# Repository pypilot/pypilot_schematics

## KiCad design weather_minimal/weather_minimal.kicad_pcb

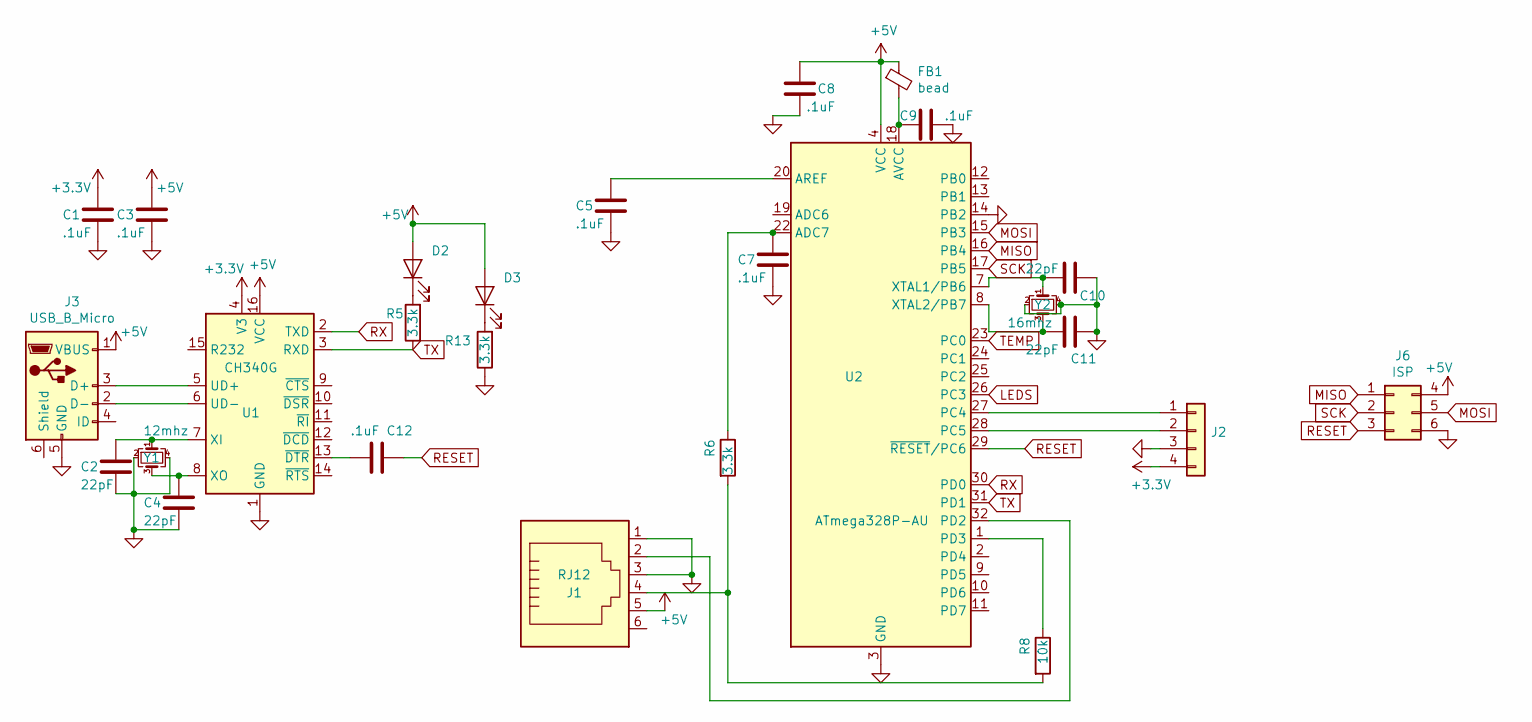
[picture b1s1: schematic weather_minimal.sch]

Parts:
C1, C3, C5, C7, C8, C9, C12: .1uF; C_0805_2012Metric; LCSC C49678
C2, C4, C10, C11: 22pF; C_0805_2012Metric; LCSC C1804
D2: LED2; LED_0805_2012Metric; LCSC C2296
D3: LED3; LED_0805_2012Metric; LCSC C84256
FB1: bead; L_0805_2012Metric; LCSC C1017
J1: RJ12; RJ12_E; LCSC C305981
J2: Conn_01x04; 1X04
J3: USB_B_Micro; USB_Mini-B_Tensility_54-00023_Vertical
J6: ISP
R5, R6, R13: 3.3k; R_0805_2012Metric; LCSC C26010
R8: 10k; R_0805_2012Metric; LCSC C17414
U1: CH340G; SOIC-16_3.9x9.9mm_P1.27mm; LCSC C14267
U2: ATmega328P-AU; TQFP-32_7x7mm_P0.8mm; LCSC C132230
Y1: 12mhz; Crystal_SMD_3225-4Pin_3.2x2.5mm; LCSC C9002
Y2: 16mhz; Crystal_SMD_3225-4Pin_3.2x2.5mm; LCSC C13738

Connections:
+3V3: C1.1, J2.4, U1.4 (V3)
+5V: C3.1, C8.2, D2.2 (A), D3.2 (A), FB1.1, J1.5, J3.1 (VBUS), J6.4, U1.16 (VCC), U2.4 (VCC), U2.6 (VCC)
GND: C1.2, C2.2, C3.2, C4.2, C5.2, C7.2, C8.1, C9.1, C10.1, C11.1, J1.1, J1.3, J2.3, J3.5 (GND), J6.6, R13.1, U1.1 (GND), U2.3 (GND), U2.5 (GND), U2.14 (PB2), U2.21 (GND), Y1.2, Y1.4, Y2.2, Y2.4
LEDS: U2.26 (PC3)
MISO: J6.1, U2.16 (PB4)
MOSI: J6.5, U2.15 (PB3)
unnamed: C2.1, U1.7 (XI), Y1.1
unnamed: C4.1, U1.8 (XO), Y1.3
unnamed: C5.1, U2.20 (AREF)
unnamed: C7.1, R6.1, U2.22 (ADC7)
unnamed: C9.2, FB1.2, U2.18 (AVCC)
unnamed: C10.2, U2.7 (XTAL1/PB6), Y2.1
unnamed: C11.2, U2.8 (XTAL2/PB7), Y2.3
unnamed: C12.2, U1.13 (~DTR)
unnamed: D2.1 (K), R5.2
unnamed: D3.1 (K), R13.2
unnamed: J1.2, U2.32 (PD2)
unnamed: J1.4, R6.2, R8.2
unnamed: J2.1, U2.27 (PC4)
unnamed: J2.2, U2.28 (PC5)
unnamed: J3.2 (D-), U1.6 (UD-)
unnamed: J3.3 (D+), U1.5 (UD+)
unnamed: R8.1, U2.1 (PD3)
RESET: C12.1, J6.3, U2.29 (~RESET~/PC6)
RX: U1.2 (TXD), U2.30 (PD0)
SCK: J6.2, U2.17 (PB5)
TEMP: U2.23 (PC0)
TX: R5.1, U1.3 (RXD), U2.31 (PD1)

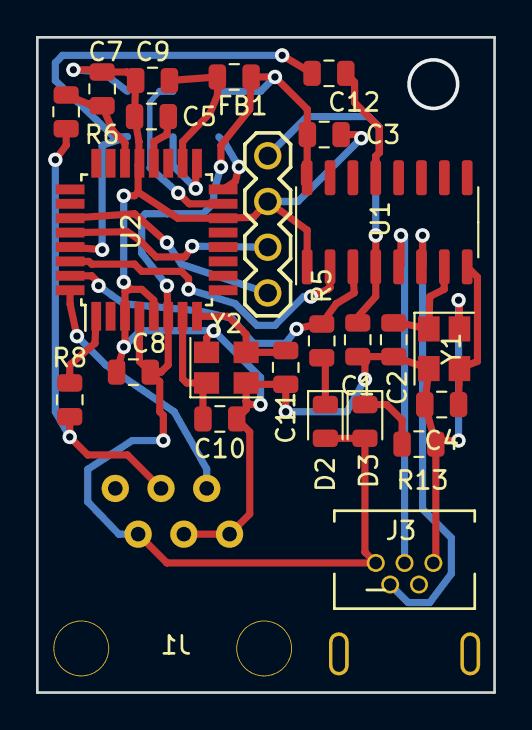
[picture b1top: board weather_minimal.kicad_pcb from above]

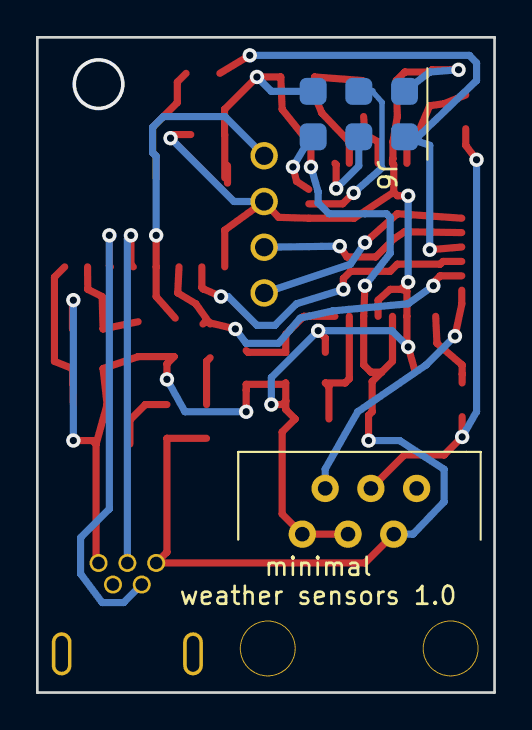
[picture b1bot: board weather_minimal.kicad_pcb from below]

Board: 2 copper layers, 25.4 x 36.4 mm, 26 parts (2 on the bottom side), 26 nets.

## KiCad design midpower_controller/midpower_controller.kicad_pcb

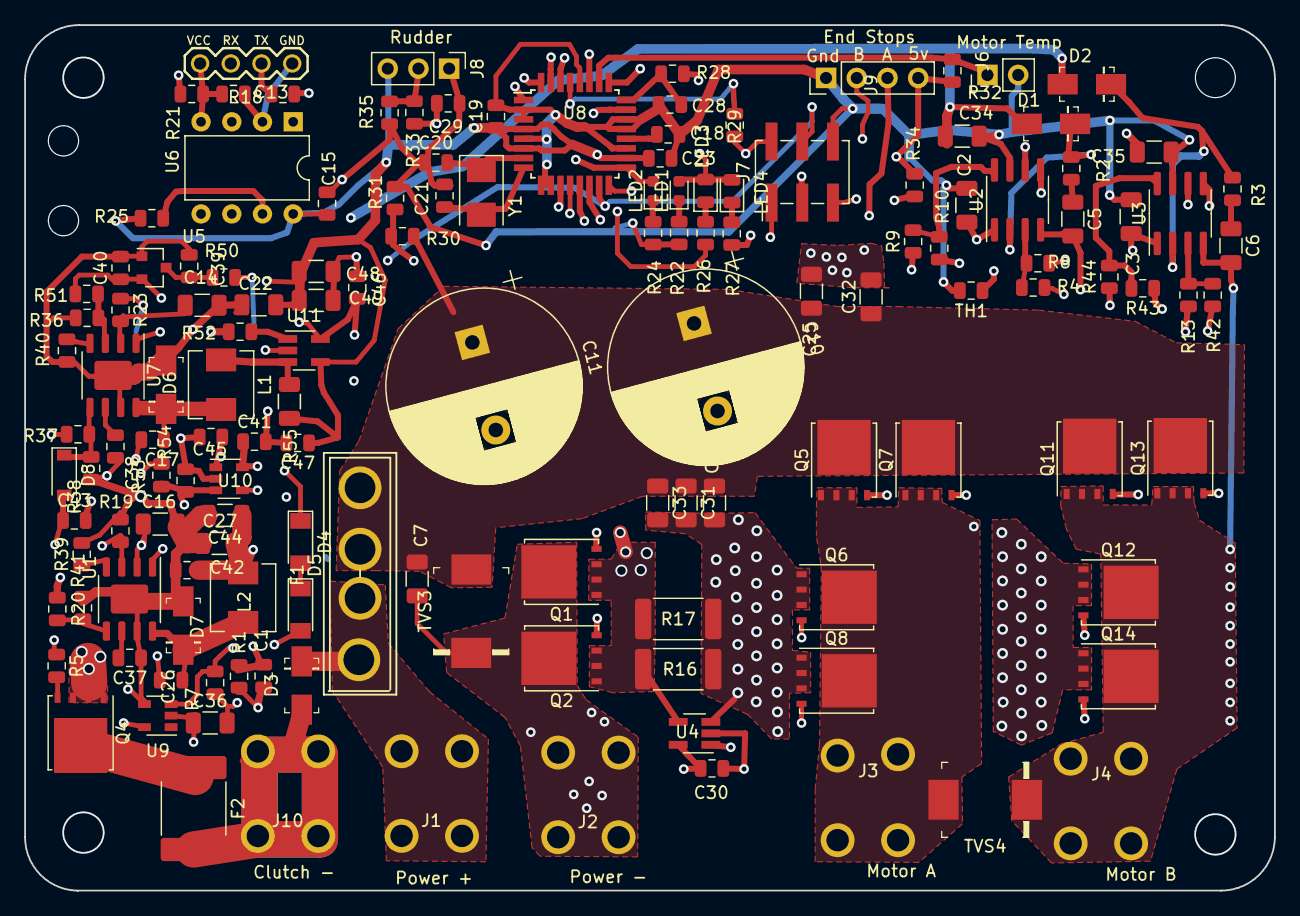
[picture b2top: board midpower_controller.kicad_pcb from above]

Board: 4 copper layers, 103.4 x 71.6 mm, 142 parts (0 on the bottom side), 81 nets.

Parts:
C1: 1uF; C_0805_2012Metric
C2, C3, C5, C6, C7, C14, C16, C22, C24, C25, C27, C31, C32, C33, C34, C35, C36, C44, C48, C49: 10uF; C_1206_3216Metric
C10, C11: 680uF; CP_Radial_D16.0mm_P7.50mm
C13, C15, C18, C19, C23, C28, C29, C30, C41, C42, C45, C46, C47: .1uF; C_0805_2012Metric
C17, C26: .22uF; C_0805_2012Metric
C20: 18pF; C_0805_2012Metric
C21: 12pF; C_0805_2012Metric
C37, C38, C43: 22nF; C_0805_2012Metric
C39, C40: 4.7uF; C_0805_2012Metric
D1: MUR160, ES1DHE3; DO-214AC
D2, D3: MUR160; DO-214AC
D4, D5: 5.6v; D_MiniMELF
D6, D7: D; DO-214AC
D8: D; D_SOD-123
F1: FUSE; BladeFuse-CarType
F2: FUSE; Fuse_2920_7451Metric
J1, J3, J4: power+; screw_terminal
J2, J10: power-; screw_terminal
J5: UART_Device; uart
J6: Conn_01x02; PinHeader_1x02_P2.54mm_Vertical
J7: ISP; PinHeader_2x03_P2.54mm_Vertical_SMD
J8: Rudder; PinHeader_1x03_P2.54mm_Vertical
J9: End Stops; PinHeader_1x04_P2.54mm_Vertical
L1, L2: 10uH; L_Sunlord_MWSA0518_5.4x5.2mm
LED1: RED; LED_0603_1608Metric
LED2: BLUE; LED_0603_1608Metric
LED3: GREEN; LED_0805_2012Metric
LED4: YELLOW; LED_0805_2012Metric
Q1, Q2, Q4, Q5, Q6, Q7, Q8, Q11, Q12, Q13, Q14: Q_NMOS_GDS; TDSON-8-1
R1, R7, R29, R32, R34, R38, R41, R52, R54: 10k; R_0805_2012Metric
R2, R3: 2.2; R_0805_2012Metric
R4, R5, R8, R9, R10, R13, R42, R43, R44: 47; R_0805_2012Metric
R16, R17: 2m; R_2512_6332Metric
R18, R50: 560; R_0805_2012Metric
R19: 120k; R_0805_2012Metric
R20: 150k; R_0805_2012Metric
R21: 2k; R_0805_2012Metric
R22, R25, R28, R33: 2.4k; R_0805_2012Metric
R23: 10; R_0805_2012Metric
R24, R26, R27: 1.2k; R_0805_2012Metric
R30, R35, R36: 100k; R_0805_2012Metric
R31: 15k; R_0805_2012Metric
R37: 56k; R_0805_2012Metric
R39, R40: 47k; R_0805_2012Metric
R51: 180k; R_0805_2012Metric
R53: 27k; R_0805_2012Metric
R55: 100m; R_1206_3216Metric
TH1: 10k NTC; R_0805_2012Metric
TVS3, TVS4: TVS; DO-214AB
U1, U7: ADP2302ARDZ; HSOP-8-1EP_3.9x4.9mm_P1.27mm_EP2.41x3.1mm
U2: UCC27201, NCP81075, UCC27211 ; NCP5183, IRS2186 b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; SOIC-8_3.9x4.9mm_P1.27mm
U3: NCP81075, UCC27211 ; NCP5183, IRS2186 backup: IRS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; SOIC-8_3.9x4.9mm_P1.27mm
U4, U11: INA180; SOT-23-5_HandSoldering
U5: AMS1117CD-5.0; SOT-23
U6: cpc5001; DIP-8_W7.62mm
U8: ATmega328P-AU; TQFP-32_7x7mm_P0.8mm
U9: MCP1416; SOT-23-5
U10: LM321; SOT-23-5
Y1: 8mhz; Crystal_SMD_5032-2Pin_5.0x3.2mm

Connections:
+5V: C15.1, C19.1, C22.1, C23.1, C30.2, C47.1, C48.1, C49.1, J7.4, J8.3, J9.4, LED1.2, LED3.2, LED4.2, R25.1, R29.2, R32.1, R34.1, R37.1, R55.1, U4.5, U6.8, U8.4, U8.6, U8.18, U11.4
+5VD: C40.1, C41.1, C46.1, R51.1, R53.2, U5.2, U10.5, U11.5
+12V: C2.1, C3.1, C27.1, C34.1, C35.1, C36.1, C42.1, C44.1, D1.2, D2.2, L2.1, R20.1, U2.1, U3.1, U9.2
/sense/PWMAH: U2.5, U8.13
/sense/PWMAL: U2.6, U8.32
/sense/PWMBH: U3.5, U8.14
/sense/PWMBL: U3.6, U8.1
/sense/Shunt: R28.1, U4.1
Controller_Temp: R34.2, TH1.1, U8.25
EndA: J9.3, U8.11
EndB: J9.2, U8.12
GND: C2.2, C3.2, C14.2, C15.2, C16.2, C18.2, C19.2, C20.1, C21.1, C22.2, C23.2, C27.2, C28.2, C29.2, C30.1, C34.2, C35.2, C36.2, C37.1, C38.1, C39.2, C40.2, C41.2, C42.2, C44.2, C45.1, C46.2, C47.2, C48.2, C49.2, D5.2, D6.2, D7.2, J6.2, J7.6, J8.1, J9.1, Q1.1, Q2.1, Q4.1, R7.1, R16.2, R17.2, R19.2, R22.2, R24.2, R31.1, R35.2, R36.2, R38.2, R39.2, R40.2, R41.2, R54.1, TH1.2, U1.7, U2.7, U3.7, U4.2, U4.4, U5.1, U6.6, U7.7, U8.2, U8.3, U8.5, U8.9, U8.10, U8.19, U8.21, U8.22, U8.28, U9.4, U10.2, U11.2
MISO: J7.1, U8.16
MOSI: J7.5, R7.2, U8.15, U9.3
Motor_Temp: J6.1, R32.2, U8.26
unnamed: C1.2, D4.1, Q1.2, Q2.2, R1.1
unnamed: C5.1, R2.2
unnamed: C5.2, J3.1, Q5.1, Q6.3, Q7.1, Q8.3, TVS4.2, U2.4
unnamed: C6.1, R3.2
unnamed: C6.2, J4.1, Q11.1, Q12.3, Q13.1, Q14.3, TVS4.1, U3.4
unnamed: C7.2, J2.1, Q1.3, Q2.3, TVS3.1
unnamed: C10.2, C11.2, C24.2, C25.2, C31.2, C32.2, C33.2, Q6.1, Q8.1, Q12.1, Q14.1, R16.1, R17.1, U4.3
unnamed: C13.1, J5.1, R21.1, U6.4
unnamed: C13.2, J5.4, U6.2
unnamed: C14.1, R23.2, U7.2
unnamed: C17.1, D6.1, L1.2, U7.8
unnamed: C17.2, U7.1
unnamed: C18.1, U8.20
unnamed: C20.2, U8.7, Y1.1
unnamed: C21.2, U8.8, Y1.2
unnamed: C26.1, D7.1, L2.2, U1.8
unnamed: C26.2, U1.1
unnamed: C28.1, R28.2, U8.24
unnamed: C37.2, U1.6
unnamed: C38.2, U7.6
unnamed: C39.1, R50.1, U5.3
unnamed: C43.1, D8.2, U10.4
unnamed: C43.2, R53.1, R54.2, U10.3
unnamed: C45.2, R52.1, U10.1
unnamed: D1.1, R2.1, U2.2
unnamed: D2.1, R3.1, U3.2
unnamed: D3.2, F2.2, J10.1
unnamed: D4.2, D5.1
unnamed: D8.1, R37.2, R38.1, U7.5
unnamed: F2.1, Q4.3
unnamed: J5.2, U6.1
unnamed: J5.3, R18.2
unnamed: J8.2, R33.1, R35.1
unnamed: L1.1, R55.2, U11.3
unnamed: LED1.1, R22.1
unnamed: LED2.1, R24.1
unnamed: LED3.1, R26.1
unnamed: LED4.1, R27.1
unnamed: Q4.2, R5.2
unnamed: Q5.2, R8.1
unnamed: Q6.2, R9.1
unnamed: Q7.2, R4.1
unnamed: Q8.2, R10.1
unnamed: Q11.2, R13.1
unnamed: Q12.2, R44.1
unnamed: Q13.2, R42.1
unnamed: Q14.2, R43.1
unnamed: R4.2, R8.2, U2.3
unnamed: R5.1, U9.5
unnamed: R9.2, R10.2, U2.8
unnamed: R13.2, R42.2, U3.3
unnamed: R18.1, R21.2, U6.3
unnamed: R20.2, R41.1, U1.5
unnamed: R36.1, R51.2, U7.3
unnamed: R39.1, U1.4
unnamed: R40.1, U7.4
unnamed: R43.2, R44.2, U3.8
unnamed: R52.2, U11.1
RESET: J7.3, R29.1, U8.29
RX: R25.2, R27.2, U6.7, U8.30
Rudder: C29.1, R33.2, U8.27
SCK: J7.2, LED2.2, R19.1, U1.3, U8.17
TX: R26.2, U6.5, U8.31
VCC: C1.1, C7.1, C10.1, C11.1, C16.1, C24.1, C25.1, C31.1, C32.1, C33.1, F1.2, Q5.3, Q7.3, Q11.3, Q13.3, R1.2, R23.1, R30.1, R50.2, TVS3.2, U1.2
VDD: D3.1, F1.1, J1.1
Voltage: R30.2, R31.2, U8.23

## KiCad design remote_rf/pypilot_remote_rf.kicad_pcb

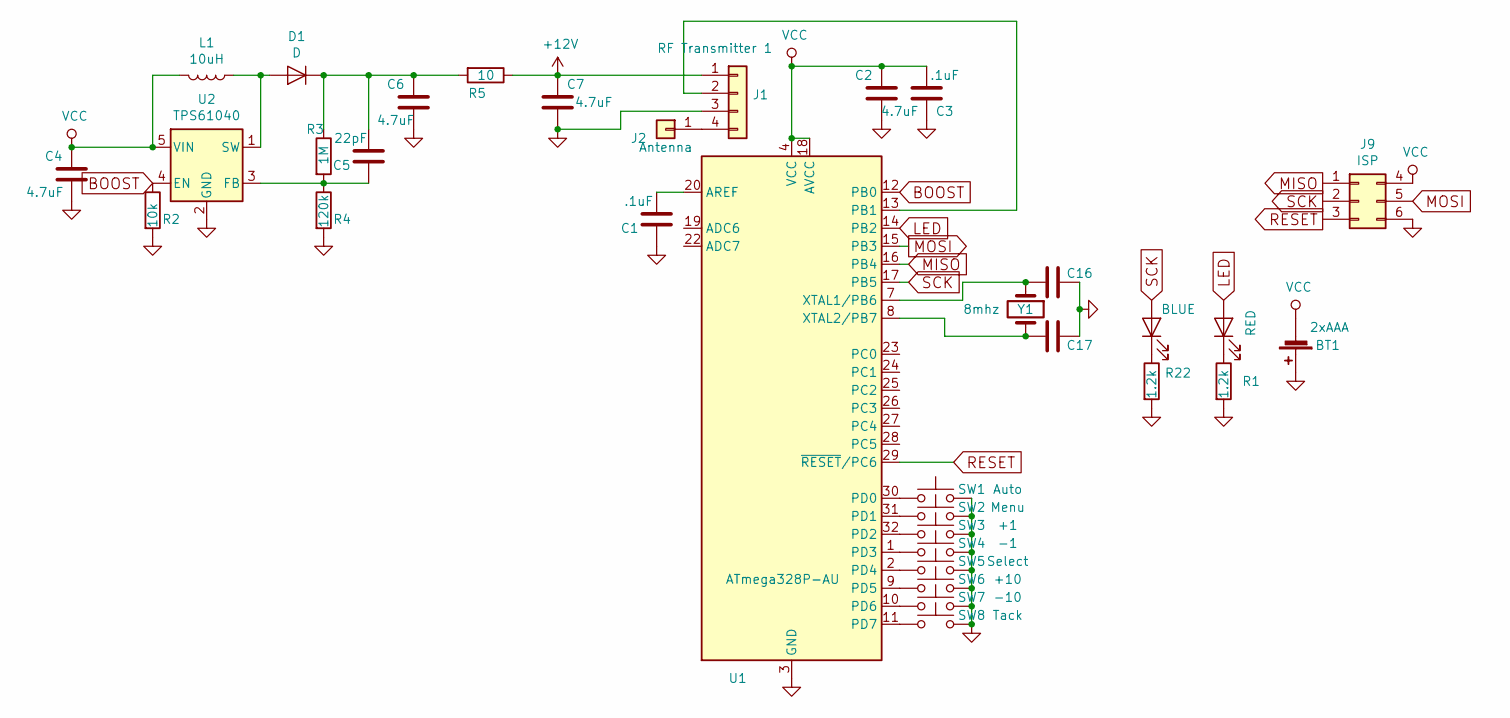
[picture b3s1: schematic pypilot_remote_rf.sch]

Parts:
BT1: 2xAAA; BatteryHolder_Keystone_2468_2xAAA
C1, C3: .1uF; C_0805_2012Metric; LCSC C49678
C2, C4, C6, C7: 4.7uF; C_1206_3216Metric; LCSC C29823
C5: 22pF; C_0805_2012Metric; LCSC C1804
C16: 18pF; C_0805_2012Metric; LCSC C1797
C17: 18pF; C_0805_2012Metric; LCSC C1792
D1: D; D_SOD-123; LCSC C8598
J1: RF Transmitter 1; PinHeader_1x04_P2.54mm_Vertical
J2: Antenna; PinHeader_1x01_P2.54mm_Vertical
J9: ISP
L1: 10uH; L_Sunlord_MWSA0518_5.4x5.2mm; LCSC C408349
LED1: RED; LED_0805_2012Metric; LCSC C84256
LED2: BLUE; LED_0805_2012Metric; LCSC C2293
R1, R22: 1.2k; R_0805_2012Metric; LCSC C17379
R2: 10k; R_0805_2012Metric; LCSC C17414
R3: 1M; R_0805_2012Metric; LCSC C17514
R4: 120k; R_0805_2012Metric; LCSC C17436
R5: 10; R_0805_2012Metric; LCSC C17415
SW1: Auto; SW_SPST_EVQQ2; LCSC C318889
SW2: Menu; SW_SPST_EVQQ2; LCSC C318889
SW3: +1; SW_SPST_EVQQ2; LCSC C318889
SW4: -1; SW_SPST_EVQQ2; LCSC C318889
SW5: Select; SW_SPST_EVQQ2; LCSC C318889
SW6: +10; SW_SPST_EVQQ2; LCSC C318889
SW7: -10; SW_SPST_EVQQ2; LCSC C318889
SW8: Tack; SW_SPST_EVQQ2; LCSC C318889
U1: ATmega328P-AU; TQFP-32_7x7mm_P0.8mm; LCSC 14877
U2: TPS61040; SOT-23-5; LCSC C9846
Y1: 8mhz; Crystal_SMD_5032-2Pin_5.0x3.2mm; LCSC C115962

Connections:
+12V: C7.1, J1.1, R5.1
BOOST: R2.1, U1.12 (PB0), U2.4 (EN)
GND: BT1.1 (+), C1.1, C2.2, C3.1, C4.2, C6.2, C7.2, C16.1, C17.1, J1.3, J9.6, R1.2, R2.2, R4.2, R22.2, SW1.2, SW2.2, SW3.2, SW4.2, SW5.2, SW6.2, SW7.2, SW8.2, U1.3 (GND), U1.5 (GND), U1.21 (GND), U2.2 (GND)
LED: LED1.2 (A), U1.14 (PB2)
MISO: J9.1, U1.16 (PB4)
MOSI: J9.5, U1.15 (PB3)
unnamed: C1.2, U1.20 (AREF)
unnamed: C5.1, R3.2, R4.1, U2.3 (FB)
unnamed: C5.2, C6.1, D1.1 (K), R3.1, R5.2
unnamed: C16.2, U1.7 (XTAL1/PB6), Y1.1
unnamed: C17.2, U1.8 (XTAL2/PB7), Y1.2
unnamed: D1.2 (A), L1.1, U2.1 (SW)
unnamed: J1.2, U1.13 (PB1)
unnamed: J1.4, J2.1
unnamed: LED1.1 (K), R1.1
unnamed: LED2.1 (K), R22.1
unnamed: SW1.1, U1.30 (PD0)
unnamed: SW2.1, U1.31 (PD1)
unnamed: SW3.1, U1.32 (PD2)
unnamed: SW4.1, U1.1 (PD3)
unnamed: SW5.1, U1.2 (PD4)
unnamed: SW6.1, U1.9 (PD5)
unnamed: SW7.1, U1.10 (PD6)
unnamed: SW8.1, U1.11 (PD7)
RESET: J9.3, U1.29 (~RESET~/PC6)
SCK: J9.2, LED2.2 (A), U1.17 (PB5)
VCC: BT1.2 (-), C2.1, C3.2, C4.1, J9.4, L1.2, U1.4 (VCC), U1.6 (VCC), U1.18 (AVCC), U2.5 (VIN)

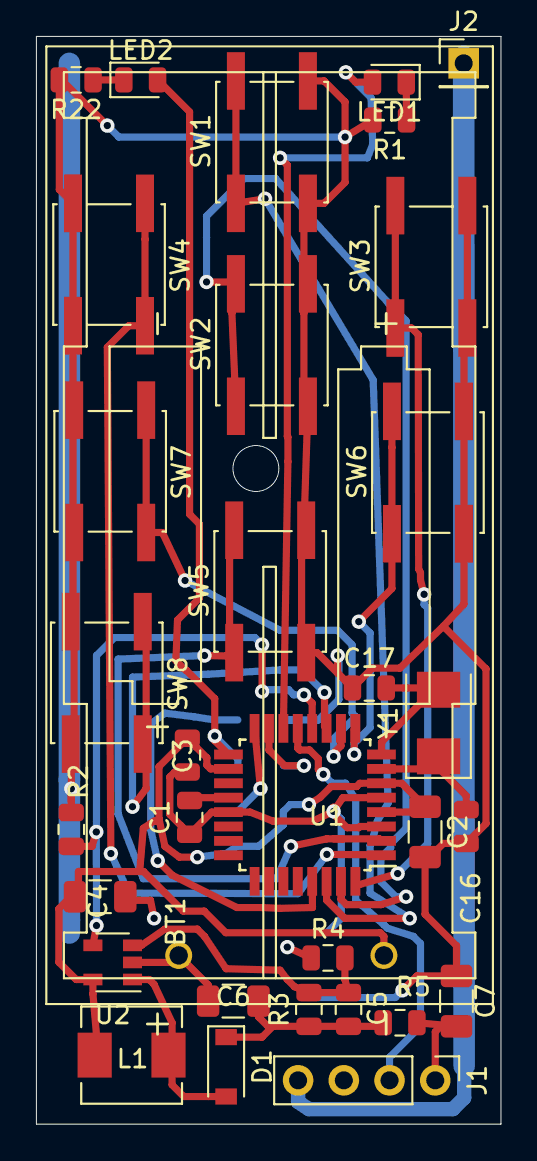
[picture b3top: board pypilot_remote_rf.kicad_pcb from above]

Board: 2 copper layers, 25.8 x 60.4 mm, 34 parts (1 on the bottom side), 27 nets.

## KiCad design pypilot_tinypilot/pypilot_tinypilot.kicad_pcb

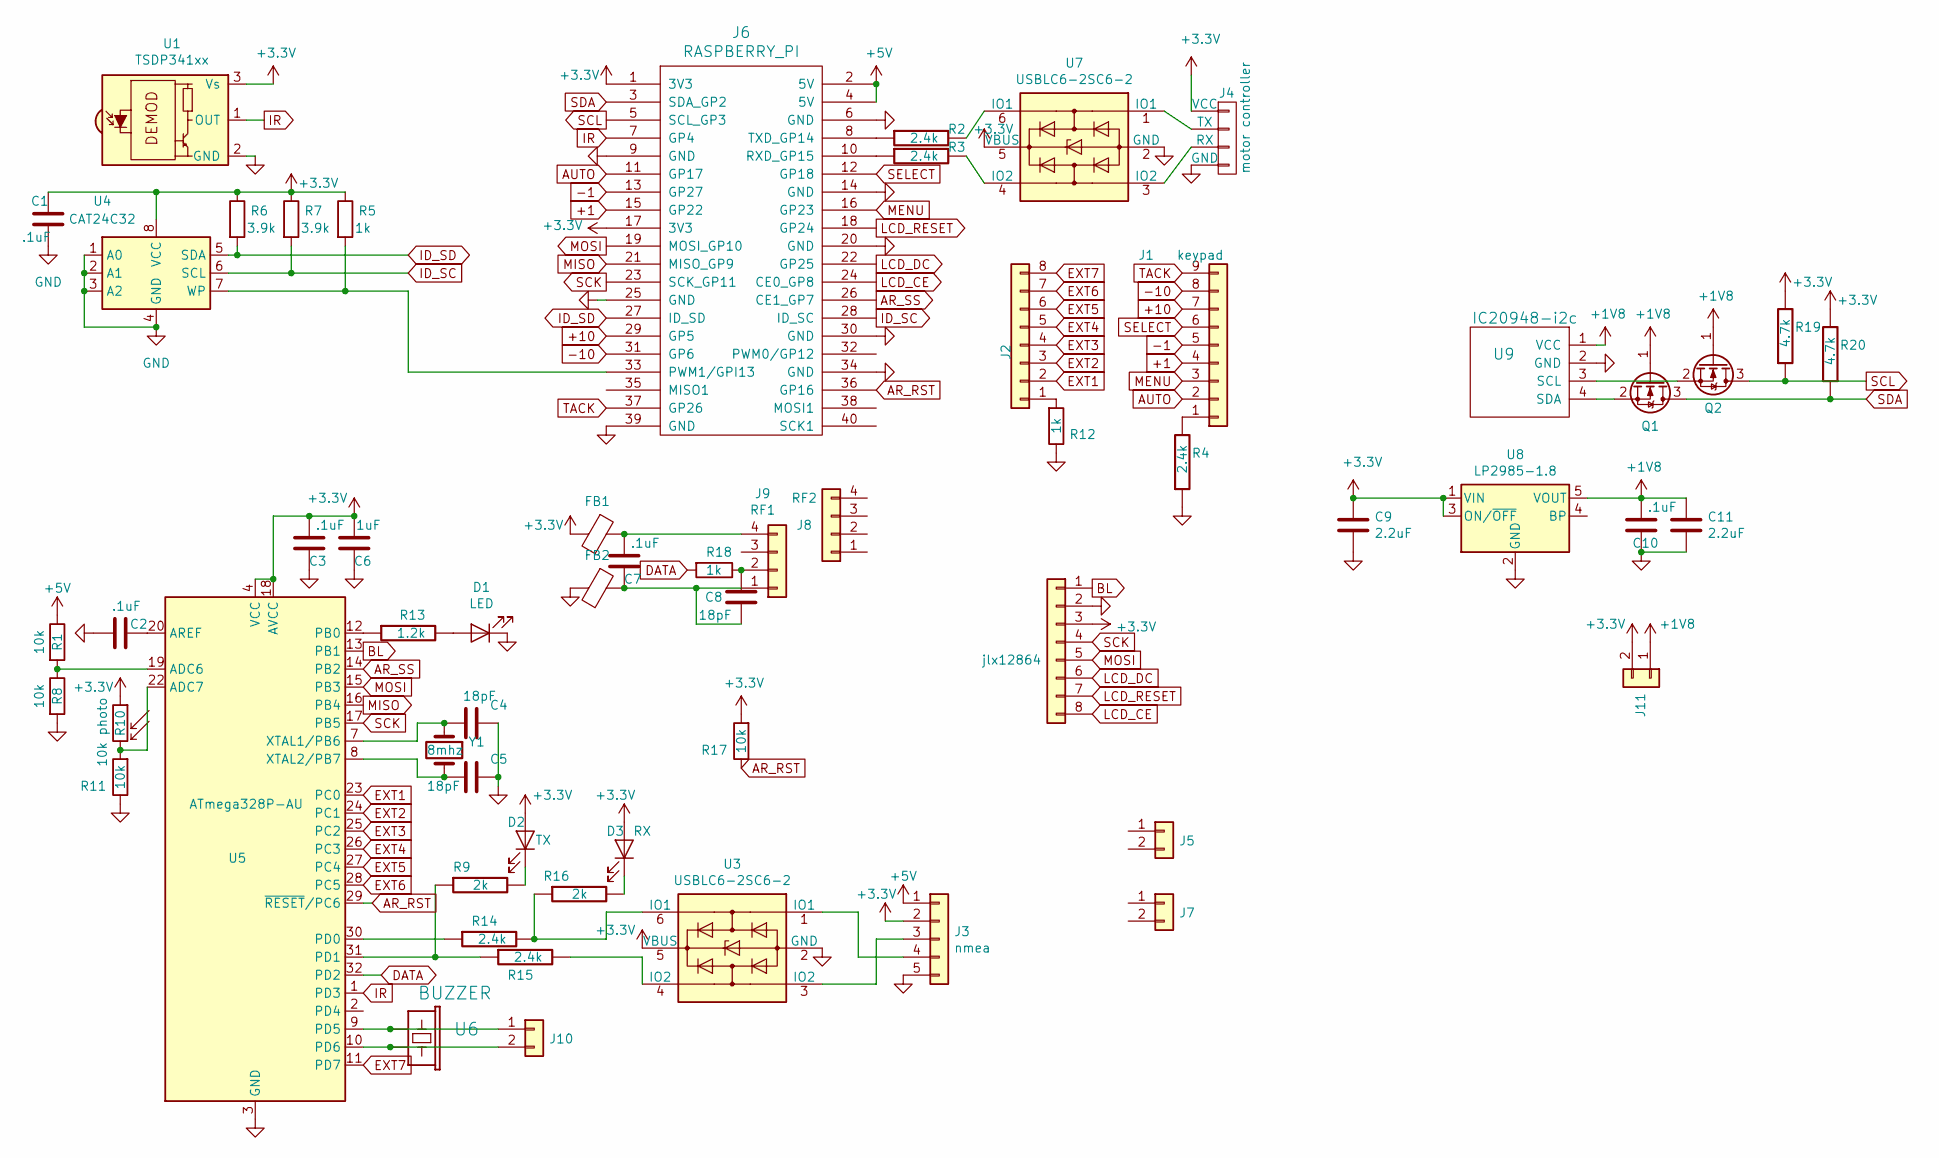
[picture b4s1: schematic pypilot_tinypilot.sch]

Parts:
C1, C2, C3, C7, C10: .1uF; C_0805_2012Metric; LCSC C49678
C4, C5, C8: 18pF; C_0805_2012Metric; LCSC C1792
C6: 1uF; C_0805_2012Metric; LCSC C28323
C9, C11: 2.2uF; C_0805_2012Metric; LCSC C49217
D1: LED; LED_0805_2012Metric; LCSC C2293
D2: TX; LED_0805_2012Metric; LCSC C2297
D3: RX; LED_0805_2012Metric; LCSC C2296
FB1, FB2: Ferrite_Bead; L_0805_2012Metric; LCSC C1017
J1: keypad
J2: Conn_01x08; PinHeader_1x08_P2.54mm_Vertical
J3: nmea; PinHeader_1x05_P2.54mm_Vertical
J4: motor controller; uart_host
J5, J7: Conn_01x02; PinHeader_1x02_P2.54mm_Vertical; LCSC C160332
J6: RASPBERRY_PI; RASPBERRY_PI_HAT
J8: RF2; PinHeader_1x04_P2.54mm_Vertical
J9: RF1; PinHeader_1x04_P2.54mm_Vertical
J10: Conn_01x02; PinHeader_1x02_P2.00mm_Vertical
J11: Conn_01x02; SolderJumper-2_P1.3mm_Open_RoundedPad1.0x1.5mm
J12: jlx12864; PinHeader_1x08_P2.54mm_Vertical; LCSC C706880
Q1, Q2: Q_NMOS_GSD; SOT-23; LCSC C255592
R1, R8, R11, R17: 10k; R_0805_2012Metric; LCSC C17414
R2, R3, R4, R14, R15: 2.4k; R_0805_2012Metric; LCSC C17526
R5, R12, R18: 1k; R_0805_2012Metric; LCSC C17513
R6, R7: 3.9k; R_0805_2012Metric; LCSC C17614
R9, R16: 2k; R_0805_2012Metric; LCSC C17604
R10: 10k photo; R_LDR_4.9x4.2mm_P2.54mm_Vertical; LCSC C10082
R13: 1.2k; R_0805_2012Metric; LCSC C17379
R19, R20: 4.7k; R_0805_2012Metric; LCSC C17673
U1: TSDP341xx; PinHeader_1x03_P2.54mm_Vertical; LCSC C264257
U3, U7: USBLC6-2SC6-2; SOT-23-6; LCSC C7519
U4: CAT24C32; SOIC-8_3.9x4.9mm_P1.27mm; LCSC C81193
U5: ATmega328P-AU; TQFP-32_7x7mm_P0.8mm; LCSC C14877
U6: BUZZER; PUIAudio_SMT_0825_S_4_R; LCSC C94599
U8: LP2985-1.8; SOT-23-5; LCSC C160916
U9: IC20948-i2c; PinSocket_1x04_P2.54mm_Vertical
Y1: 8mhz; Crystal_SMD_5032-2Pin_5.0x3.2mm; LCSC C115962

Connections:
+1: J1.4, J6.15 (GP22)
+1V8: C10.2, C11.1, J11.1, Q1.1 (G), Q2.1 (G), U8.5 (VOUT), U9.1 (VCC)
+3V3: C1.1, C3.2, C6.2, C9.1, D2.2 (A), D3.2 (A), FB1.2, J3.2, J4.1 (VCC), J6.1 (3V3), J6.17 (3V3), J11.2, J12.3, R5.1, R6.1, R7.1, R10.1, R17.2, R19.2, R20.2, U1.3 (Vs), U3.5 (VBUS), U4.8 (VCC), U5.4 (VCC), U5.6 (VCC), U5.18 (AVCC), U7.5 (VBUS), U8.1 (VIN), U8.3 (ON/~OFF~); also elsewhere on the board
+5V: J3.1, J6.2 (5V), J6.4 (5V), R1.1
+10: J1.7, J6.29 (GP5)
-1: J1.5, J6.13 (GP27)
-10: J1.8, J6.31 (GP6)
AR_RST: J6.36 (GP16), R17.1, U5.29 (~RESET~/PC6)
AR_SS: J6.26 (CE1_GP7), U5.14 (PB2)
AUTO: J1.2, J6.11 (GP17)
BL: J12.1, U5.13 (PB1); also elsewhere on the board
DATA: R18.2, U5.32 (PD2)
EXT1: J2.2, U5.23 (PC0)
EXT2: J2.3, U5.24 (PC1)
EXT3: J2.4, U5.25 (PC2)
EXT4: J2.5, U5.26 (PC3)
EXT5: J2.6, U5.27 (PC4)
EXT6: J2.7, U5.28 (PC5)
EXT7: J2.8, U5.11 (PD7)
GND: C1.2, C2.2, C3.1, C4.1, C5.1, C6.1, C9.2, C10.1, C11.2, D1.1 (K), FB2.2, J3.5, J4.4 (GND), J6.6 (GND), J6.9 (GND), J6.14 (GND), J6.20 (GND), J6.25 (GND), J6.30 (GND), J6.34 (GND), J6.39 (GND), J12.2, R4.1, R8.2, R11.1, R12.1, U1.2 (GND), U3.2 (GND), U4.1 (A0), U4.2 (A1), U4.3 (A2), U4.4 (GND), U5.3 (GND), U5.5 (GND), U5.21 (GND), U7.2 (GND), U8.2 (GND), U9.2 (GND); also elsewhere on the board
ID_SC: J6.28 (ID_SC), R7.2, U4.6 (SCL)
ID_SD: J6.27 (ID_SD), R6.2, U4.5 (SDA)
IR: J6.7 (GP4), U1.1 (OUT), U5.1 (PD3)
LCD_CE: J6.24 (CE0_GP8), J12.8; also elsewhere on the board
LCD_DC: J6.22 (GP25), J12.6; also elsewhere on the board
LCD_RESET: J6.18 (GP24), J12.7; also elsewhere on the board
MENU: J1.3, J6.16 (GP23)
MISO: J6.21 (MISO_GP9), U5.16 (PB4)
MOSI: J6.19 (MOSI_GP10), J12.5, U5.15 (PB3); also elsewhere on the board
unnamed: C2.1, U5.20 (AREF)
unnamed: C4.2, U5.7 (XTAL1/PB6), Y1.1
unnamed: C5.2, U5.8 (XTAL2/PB7), Y1.2
unnamed: C7.1, C8.1, FB2.1, J9.1
unnamed: C7.2, FB1.1, J9.4
unnamed: C8.2, J9.2, R18.1
unnamed: D1.2 (A), R13.2
unnamed: D2.1 (K), R9.2
unnamed: D3.1 (K), R16.2
unnamed: J1.1, R4.2
unnamed: J2.1, R12.2
unnamed: J3.3, U3.3 (IO2)
unnamed: J3.4, U3.1 (IO1)
unnamed: J4.2 (TX), U7.1 (IO1)
unnamed: J4.3 (RX), U7.3 (IO2)
unnamed: J6.8 (TXD_GP14), R2.1
unnamed: J6.10 (RXD_GP15), R3.1
unnamed: J6.33 (PWM1/GPI13), R5.2, U4.7 (WP)
unnamed: J10.1, U5.9 (PD5), U6.2 (GND)
unnamed: J10.2, U5.10 (PD6), U6.1 (POS)
unnamed: Q1.2 (S), U9.4 (SDA)
unnamed: Q2.2 (S), U9.3 (SCL)
unnamed: R1.2, R8.1, U5.19 (ADC6)
unnamed: R2.2, U7.6 (IO1)
unnamed: R3.2, U7.4 (IO2)
unnamed: R10.2, R11.2, U5.22 (ADC7)
unnamed: R13.1, U5.12 (PB0)
unnamed: R14.1, U5.30 (PD0)
unnamed: R14.2, R16.1, U3.6 (IO1)
unnamed: R9.1, R15.1, U5.31 (PD1)
unnamed: R15.2, U3.4 (IO2)
SCK: J6.23 (SCK_GP11), J12.4, U5.17 (PB5); also elsewhere on the board
SCL: J6.5 (SCL_GP3), Q2.3 (D), R19.1
SDA: J6.3 (SDA_GP2), Q1.3 (D), R20.1
SELECT: J1.6, J6.12 (GP18)
TACK: J1.9, J6.37 (GP26)

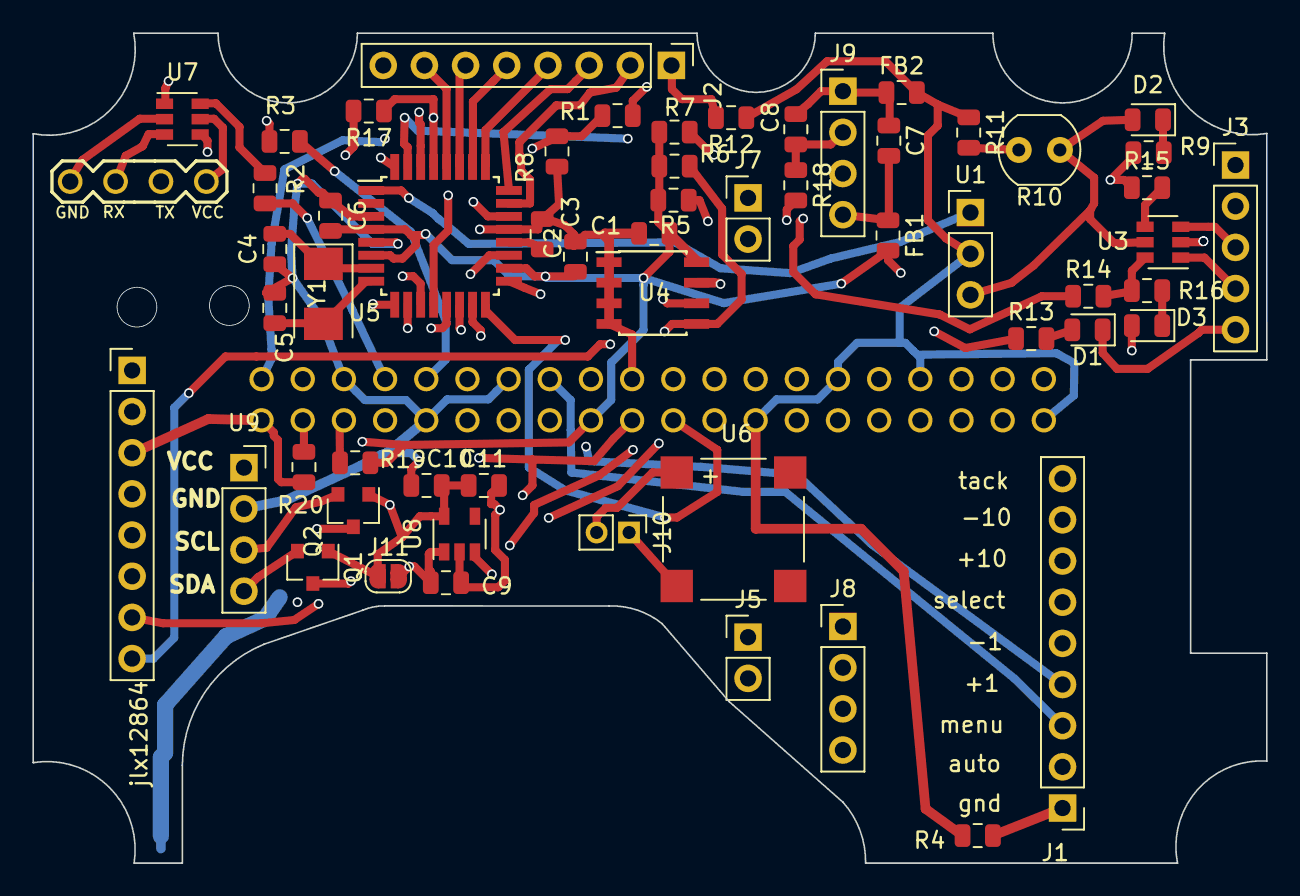
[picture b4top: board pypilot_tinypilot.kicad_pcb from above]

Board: 4 copper layers, 76.1 x 51.2 mm, 59 parts (0 on the bottom side), 65 nets.

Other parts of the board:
jlx12864: Conn_01x08; PinHeader_1x08_P2.54mm_Vertical

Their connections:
+3V3: jlx12864.3; also elsewhere on the board
BL: jlx12864.1; also elsewhere on the board
GND: jlx12864.2; also elsewhere on the board
LCD_CE: jlx12864.8; also elsewhere on the board
LCD_DC: jlx12864.6; also elsewhere on the board
LCD_RESET: jlx12864.7; also elsewhere on the board
MOSI: jlx12864.5; also elsewhere on the board
SCK: jlx12864.4; also elsewhere on the board

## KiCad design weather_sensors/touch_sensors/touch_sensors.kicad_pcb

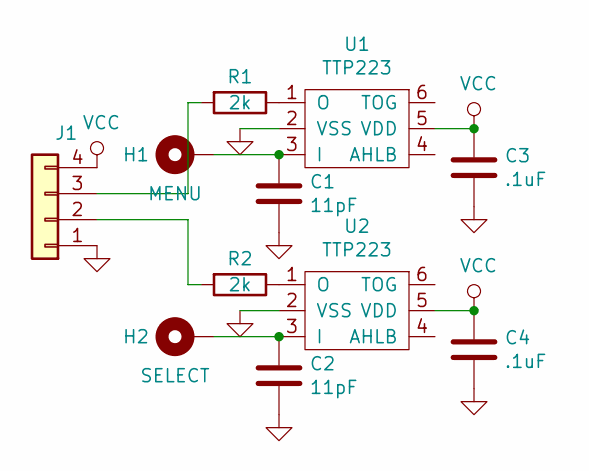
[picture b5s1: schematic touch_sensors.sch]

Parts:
C1, C2: 11pF; C_0805_2012Metric
C3, C4: .1uF; C_0805_2012Metric; LCSC C49678
H1: MENU; touchpad
H2: SELECT; touchpad
J1: Conn_01x04; PinHeader_1x04_P2.54mm_Vertical
R1, R2: 2k; R_0805_2012Metric; LCSC C17604
U1, U2: TTP223; SOT-23-6; LCSC C129459

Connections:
GND: C1.2, C2.2, C3.2, C4.2, J1.1, U1.2 (VSS), U2.2 (VSS)
unnamed: C1.1, H1.1, U1.3 (I)
unnamed: C2.1, H2.1, U2.3 (I)
unnamed: J1.2, R2.2
unnamed: J1.3, R1.2
unnamed: R1.1, U1.1 (O)
unnamed: R2.1, U2.1 (O)
VCC: C3.1, C4.1, J1.4, U1.5 (VDD), U2.5 (VDD)

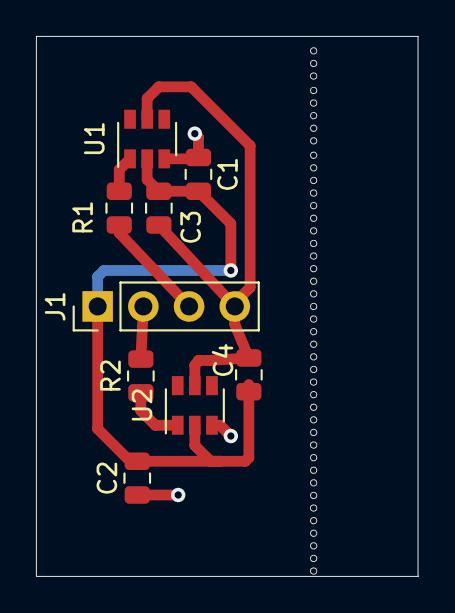
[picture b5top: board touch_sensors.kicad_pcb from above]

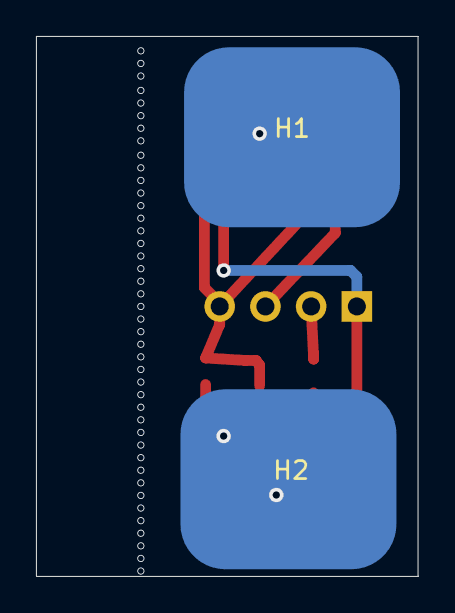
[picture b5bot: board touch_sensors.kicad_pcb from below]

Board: 2 copper layers, 21.2 x 30.0 mm, 11 parts (2 on the bottom side), 8 nets.

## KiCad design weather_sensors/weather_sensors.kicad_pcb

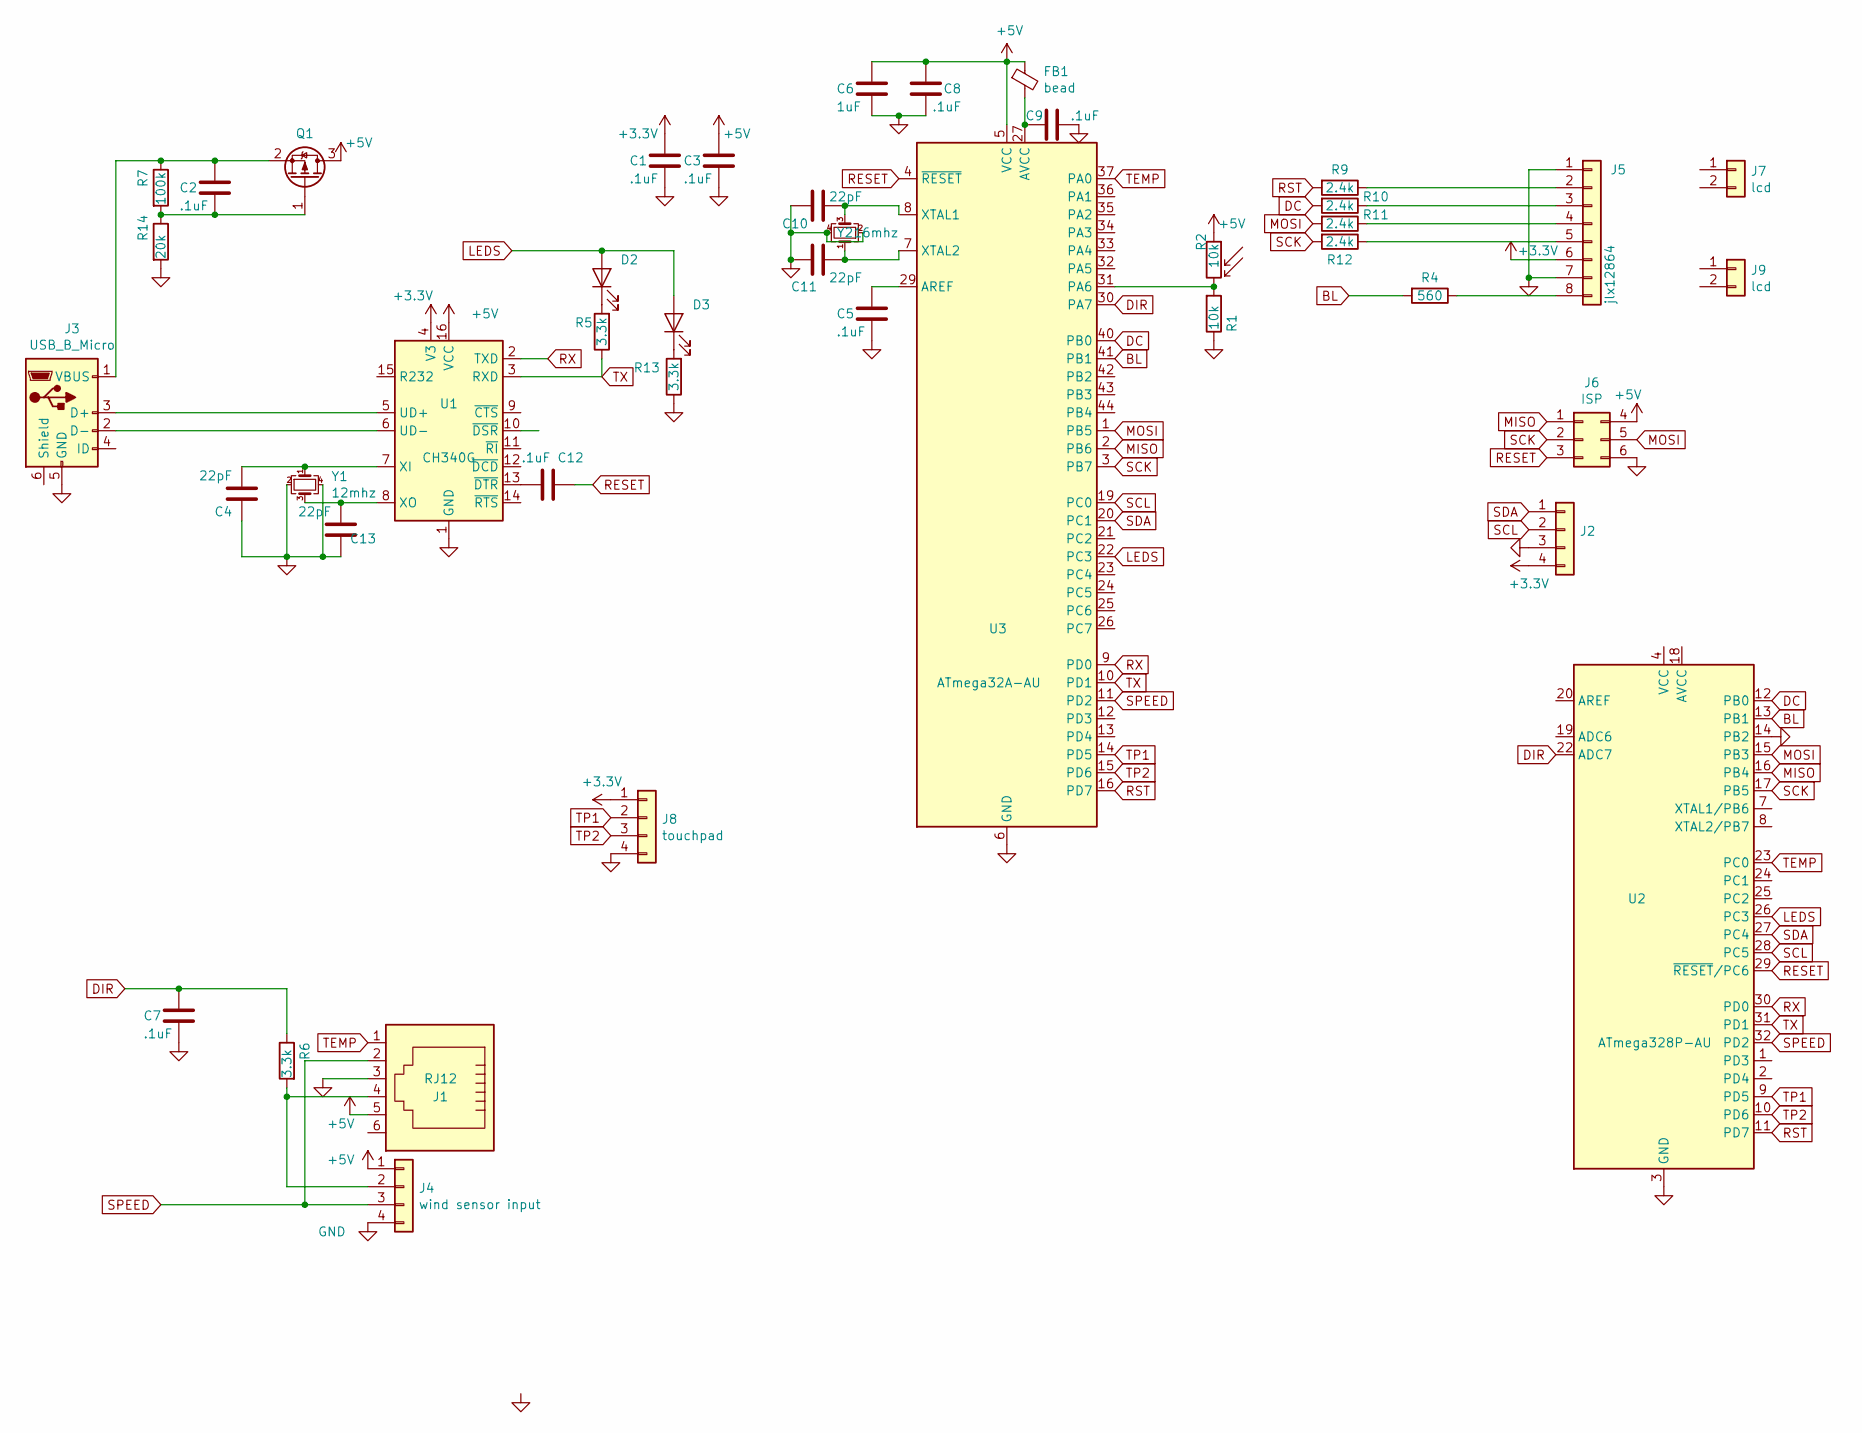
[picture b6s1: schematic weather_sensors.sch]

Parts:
C1, C2, C3, C5, C7, C8, C9, C12: .1uF; C_0805_2012Metric; LCSC C49678
C4, C10, C11, C13: 22pF; C_0805_2012Metric; LCSC C1804
C6: 1uF; C_0805_2012Metric; LCSC C28323
D2: LED2; LED_0805_2012Metric; LCSC C2296
D3: LED3; LED_0805_2012Metric; LCSC C84256
FB1: bead; L_0805_2012Metric; LCSC C1017
J1: RJ12; RJ12_E
J2: Conn_01x04; 1X04; LCSC C124378
J3: USB_B_Micro; USB_Mini-B_Tensility_54-00023_Vertical
J4: wind sensor input; 1X04
J5: jlx12864; 1X08
J6: ISP
J7, J9: lcd; 1X02
J8: touchpad; 1X04; LCSC C180218
Q1: Q_PMOS_GSD; SOT-23; LCSC C10487
R1: 10k; R_0805_2012Metric; LCSC C17414
R2: 10k; R_LDR_5.1x4.3mm_P3.4mm_Vertical
R4: 560; R_0805_2012Metric; LCSC C28636
R5, R6, R13: 3.3k; R_0805_2012Metric; LCSC C26010
R7: 100k; R_0805_2012Metric; LCSC C17407
R9, R10, R11, R12: 2.4k; R_0805_2012Metric; LCSC C17526
R14: 20k; R_0805_2012Metric; LCSC C4328
U1: CH340G; SOIC-16_3.9x9.9mm_P1.27mm; LCSC C14267
U2: ATmega328P-AU
U3: ATmega32A-AU; TQFP-44_10x10mm_P0.8mm; LCSC C5659
Y1: 12mhz; Crystal_SMD_3225-4Pin_3.2x2.5mm; LCSC C9002
Y2: 16mhz; Crystal_SMD_3225-4Pin_3.2x2.5mm; LCSC C13738

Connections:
+3V3: C1.1, J2.4, J5.6, J8.1, U1.4 (V3)
+5V: C3.1, C6.1, C8.2, FB1.1, J1.5, J4.1, J6.4, Q1.3 (D), R2.1, U1.16 (VCC), U3.5 (VCC), U3.17 (VCC), U3.38 (VCC)
BL: R4.2, U2.13 (PB1), U3.41 (PB1)
DC: R10.2, U2.12 (PB0), U3.40 (PB0)
DIR: C7.1, R6.1, U2.22 (ADC7), U3.30 (PA7)
GND: C1.2, C3.2, C4.1, C5.2, C6.2, C7.2, C8.1, C9.1, C10.1, C11.1, C13.1, J1.3, J2.3, J3.5 (GND), J4.4, J5.1, J5.7, J6.6, J8.4, R1.1, R13.1, R14.2, U1.1 (GND), U2.3 (GND), U2.5 (GND), U2.14 (PB2), U2.21 (GND), U3.6 (GND), U3.18 (GND), U3.28 (GND), U3.39 (GND), Y1.2, Y1.4, Y2.2, Y2.4
LEDS: D2.2 (A), D3.2 (A), U2.26 (PC3), U3.22 (PC3)
MISO: J6.1, U2.16 (PB4), U3.2 (PB6)
MOSI: J6.5, R11.2, U2.15 (PB3), U3.1 (PB5)
unnamed: C2.1, J3.1 (VBUS), Q1.2 (S), R7.1
unnamed: C2.2, Q1.1 (G), R7.2, R14.1
unnamed: C4.2, U1.7 (XI), Y1.1
unnamed: C5.1, U3.29 (AREF)
unnamed: C9.2, FB1.2, U3.27 (AVCC)
unnamed: C10.2, U3.8 (XTAL1), Y2.3
unnamed: C11.2, U3.7 (XTAL2), Y2.1
unnamed: C12.2, U1.13 (~DTR)
unnamed: C13.2, U1.8 (XO), Y1.3
unnamed: D2.1 (K), R5.2
unnamed: D3.1 (K), R13.2
unnamed: J1.4, J4.2, R6.2
unnamed: J3.2 (D-), U1.6 (UD-)
unnamed: J3.3 (D+), U1.5 (UD+)
unnamed: J5.2, R9.1
unnamed: J5.3, R10.1
unnamed: J5.4, R11.1
unnamed: J5.5, R12.1
unnamed: J5.8, R4.1
unnamed: R1.2, R2.2, U3.31 (PA6)
unnamed: U2.4 (VCC), U2.6 (VCC)
RESET: C12.1, J6.3, U2.29 (~RESET~/PC6), U3.4 (~RESET)
RST: R9.2, U2.11 (PD7), U3.16 (PD7)
RX: U1.2 (TXD), U2.30 (PD0), U3.9 (PD0)
SCK: J6.2, R12.2, U2.17 (PB5), U3.3 (PB7)
SCL: J2.2, U2.28 (PC5), U3.19 (PC0)
SDA: J2.1, U2.27 (PC4), U3.20 (PC1)
SPEED: J1.2, J4.3, U2.32 (PD2), U3.11 (PD2)
TEMP: J1.1, U2.23 (PC0), U3.37 (PA0)
TP1: J8.2, U2.9 (PD5), U3.14 (PD5)
TP2: J8.3, U2.10 (PD6), U3.15 (PD6)
TX: R5.1, U1.3 (RXD), U2.31 (PD1), U3.10 (PD1)
